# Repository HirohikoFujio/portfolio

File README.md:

# portfolio
## 内容物
* 3rd_year
    * late_team_dev
      * 後期チーム開発作成物 
    * seminar
      * 組込みゼミ作成物
* index
    * 作成物リンク集の予定(現在は空)

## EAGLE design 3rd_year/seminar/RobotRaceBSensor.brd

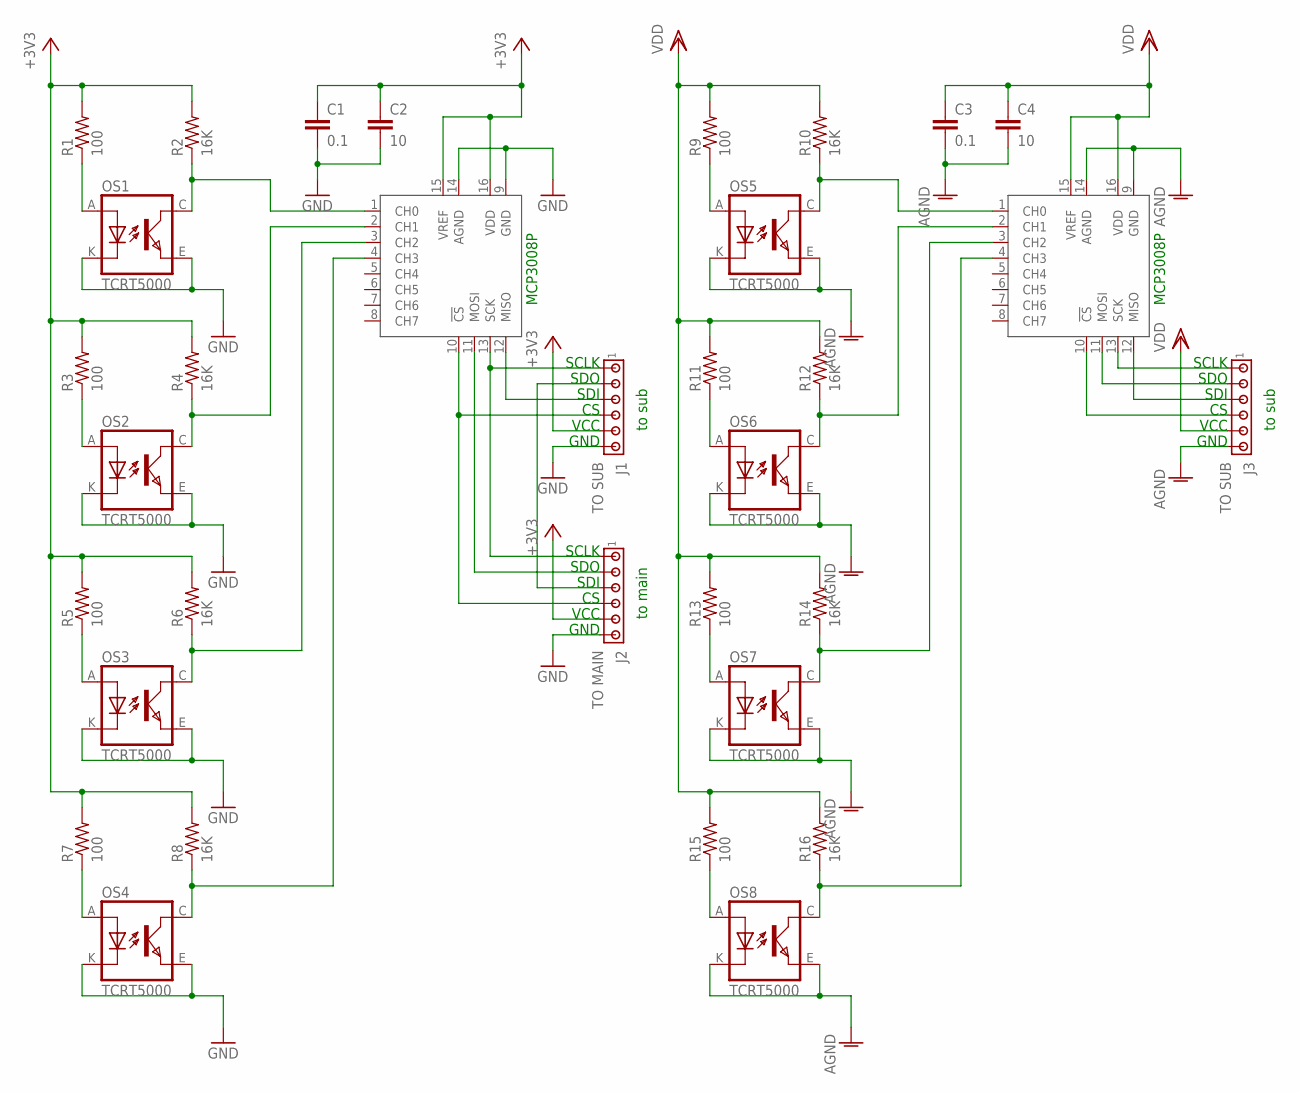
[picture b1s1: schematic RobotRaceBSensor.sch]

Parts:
C1, C3: 0.1; C0805
C2, C4: 10; C0805
J1, J3: TO SUB; 10X06MTA
J2: TO MAIN; 10X06MTA
OS1, OS2, OS3, OS4, OS5, OS6, OS7, OS8: TCRT5000
R1, R3, R5, R7, R9, R11, R13, R15: 100; R0805
R2, R4, R6, R8, R10, R12, R14, R16: 16K; R0805
U$1, U$2: MCP3008P; DIL16

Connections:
+3V3: C1.1, C2.1, J1.5, J2.5, R1.2, R2.2, R3.2, R4.2, R5.2, R6.2, R7.2, R8.2, U$1.15 (VREF), U$1.16 (VDD)
AGND: C3.2, C4.2, J3.6, OS5.E (EMITTER), OS5.K (CATHODE), OS6.E (EMITTER), OS6.K (CATHODE), OS7.E (EMITTER), OS7.K (CATHODE), OS8.E (EMITTER), OS8.K (CATHODE), U$2.9 (GND), U$2.14 (AGND)
GND: C1.2, C2.2, J1.6, J2.6, OS1.E (EMITTER), OS1.K (CATHODE), OS2.E (EMITTER), OS2.K (CATHODE), OS3.E (EMITTER), OS3.K (CATHODE), OS4.E (EMITTER), OS4.K (CATHODE), U$1.9 (GND), U$1.14 (AGND)
unnamed: OS1.A (ANODE), R1.1
unnamed: OS1.C (COLLECTOR), R2.1, U$1.1 (CH0)
unnamed: J1.1, J2.1, U$1.13 (SCK)
unnamed: OS2.A (ANODE), R3.1
unnamed: OS2.C (COLLECTOR), R4.1, U$1.2 (CH1)
unnamed: J1.3, U$1.12 (MISO)
unnamed: OS3.A (ANODE), R5.1
unnamed: OS3.C (COLLECTOR), R6.1, U$1.3 (CH2)
unnamed: J1.2, J2.3
unnamed: OS4.A (ANODE), R7.1
unnamed: OS4.C (COLLECTOR), R8.1, U$1.4 (CH3)
unnamed: J1.4, J2.4, U$1.10 (!CS)
unnamed: J2.2, U$1.11 (MOSI)
unnamed: OS5.A (ANODE), R9.1
unnamed: OS5.C (COLLECTOR), R10.1, U$2.1 (CH0)
unnamed: OS6.A (ANODE), R11.1
unnamed: OS6.C (COLLECTOR), R12.1, U$2.2 (CH1)
unnamed: OS7.A (ANODE), R13.1
unnamed: OS7.C (COLLECTOR), R14.1, U$2.3 (CH2)
unnamed: OS8.A (ANODE), R15.1
unnamed: OS8.C (COLLECTOR), R16.1, U$2.4 (CH3)
unnamed: J3.1, U$2.13 (SCK)
unnamed: J3.3, U$2.12 (MISO)
unnamed: J3.2, U$2.11 (MOSI)
unnamed: J3.4, U$2.10 (!CS)
VDD: C3.1, C4.1, J3.5, R9.2, R10.2, R11.2, R12.2, R13.2, R14.2, R15.2, R16.2, U$2.15 (VREF), U$2.16 (VDD)

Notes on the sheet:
SCLK
SDO
SDI
VCC
GND
MCP3008P
to main
to sub

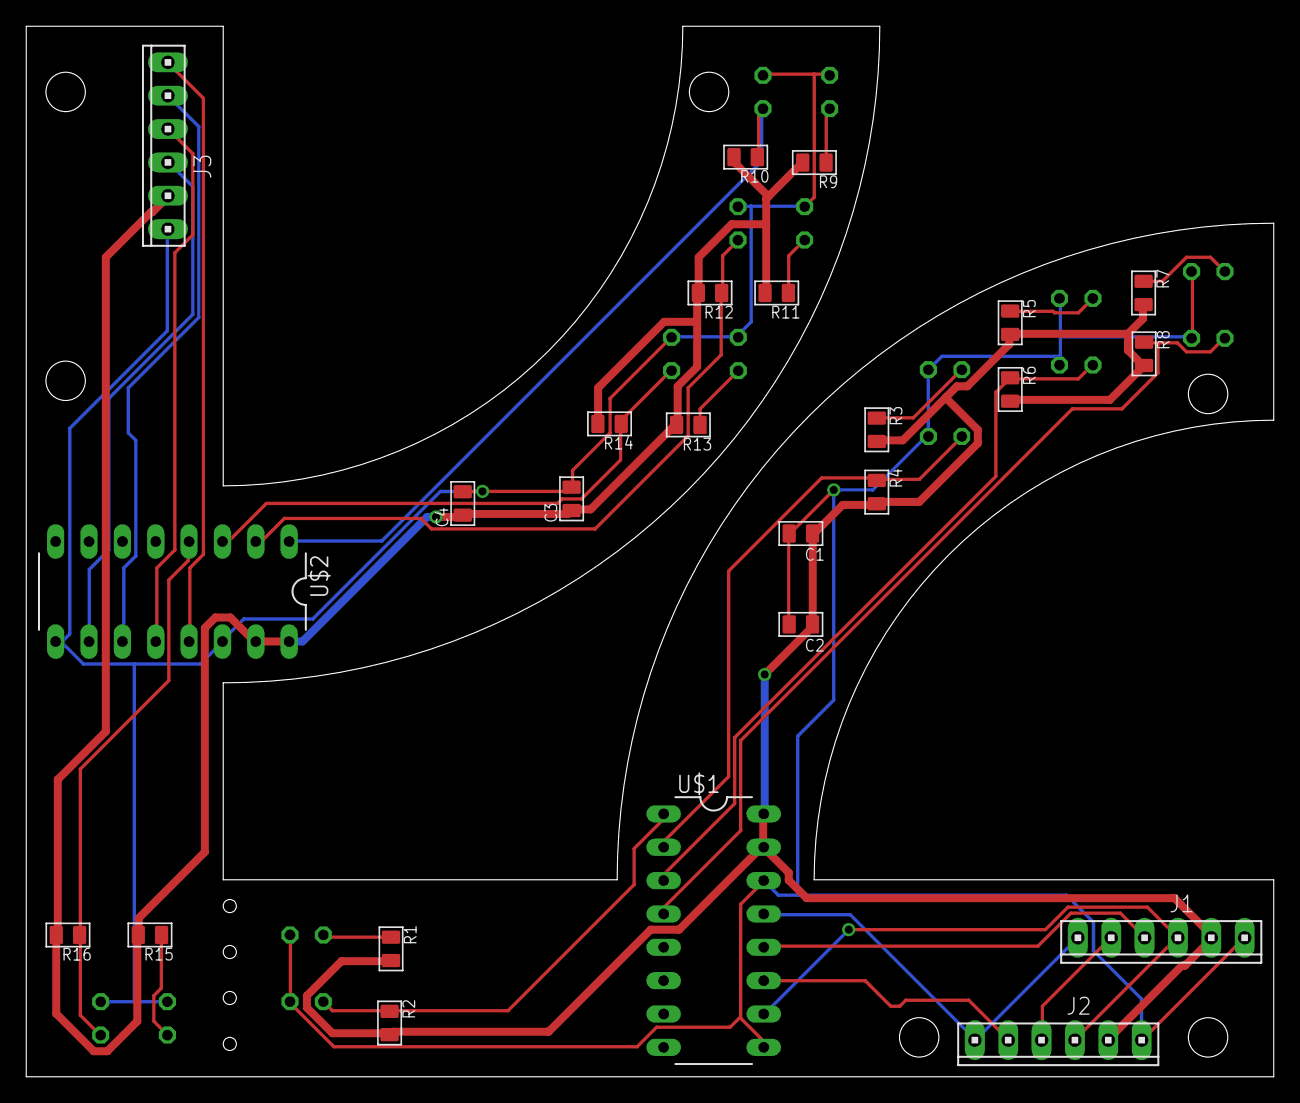
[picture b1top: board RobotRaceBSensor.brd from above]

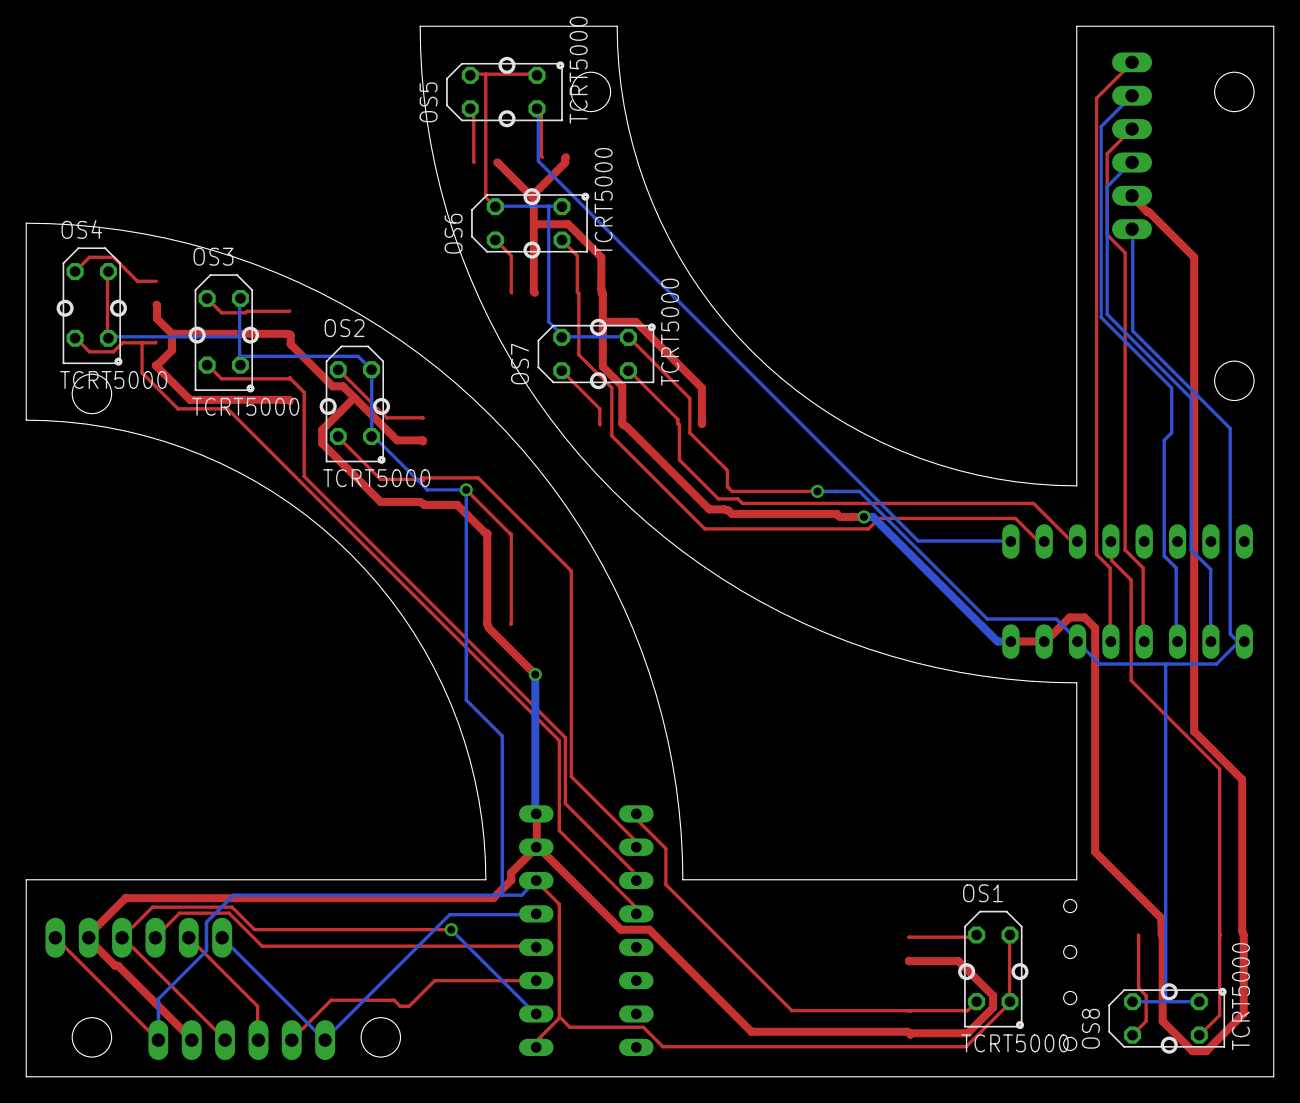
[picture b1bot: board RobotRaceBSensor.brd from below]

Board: 2 copper layers, 95.0 x 80.0 mm, 33 parts (8 on the bottom side), 29 nets.

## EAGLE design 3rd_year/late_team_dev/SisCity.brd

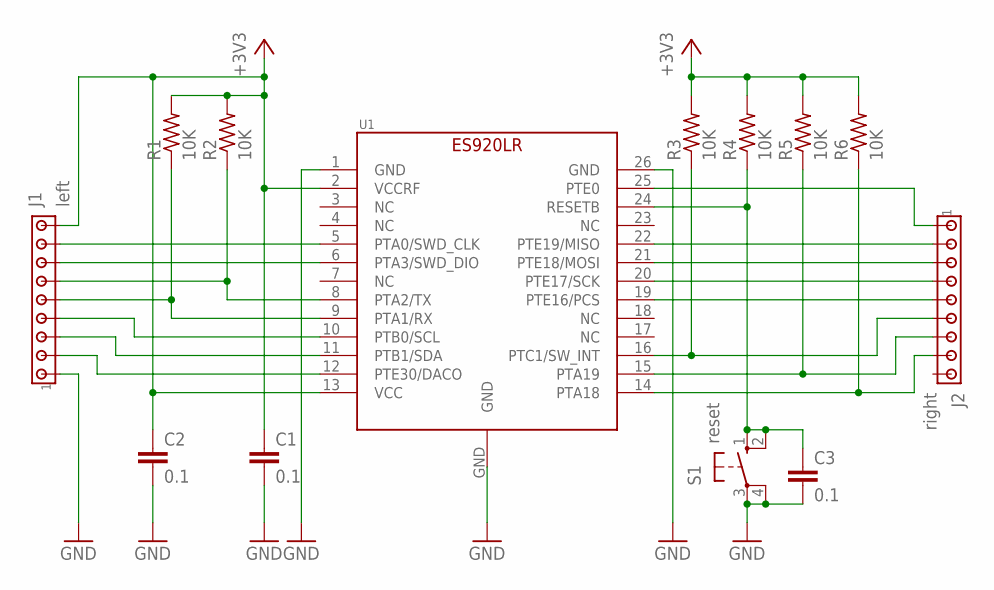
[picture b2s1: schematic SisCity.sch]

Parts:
C1, C2, C3: 0.1; C0805
J1: left; 10X09MTA
J2: right; 10X09MTA
R1, R2, R3, R4, R5, R6: 10K; M0805
S1: reset; B3F-10XX
U1: ES920LR

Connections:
+3V3: C1.1, C2.1, J1.9, R1.2, R2.2, R3.2, R4.2, R5.2, R6.2, U1.2 (VCCRF), U1.13 (VCC)
GND: C1.2, C2.2, C3.2, J1.1, S1.3, S1.4 (P1), U1.1 (GND), U1.26 (GND), U1.GND
unnamed: J1.8, U1.5 (PTA0/SWD_CLK)
unnamed: J1.7, U1.6 (PTA3/SWD_DIO)
unnamed: J1.4, U1.10 (PTB0/SCL)
unnamed: J1.6, R2.1, U1.8 (PTA2/TX)
unnamed: J1.5, R1.1, U1.9 (PTA1/RX)
unnamed: J1.3, U1.11 (PTB1/SDA)
unnamed: J1.2, U1.12 (PTE30/DACO)
unnamed: J2.1, U1.25 (PTE0)
unnamed: J2.2, U1.22 (PTE19/MISO)
unnamed: J2.3, U1.21 (PTE18/MOSI)
unnamed: J2.4, U1.20 (PTE17/SCK)
unnamed: J2.5, U1.19 (PTE16/PCS)
unnamed: J2.8, R6.1, U1.14 (PTA18)
unnamed: J2.7, R5.1, U1.15 (PTA19)
unnamed: J2.6, R3.1, U1.16 (PTC1/SW_INT)
unnamed: C3.1, R4.1, S1.1 (S), S1.2 (S1), U1.24 (RESETB)

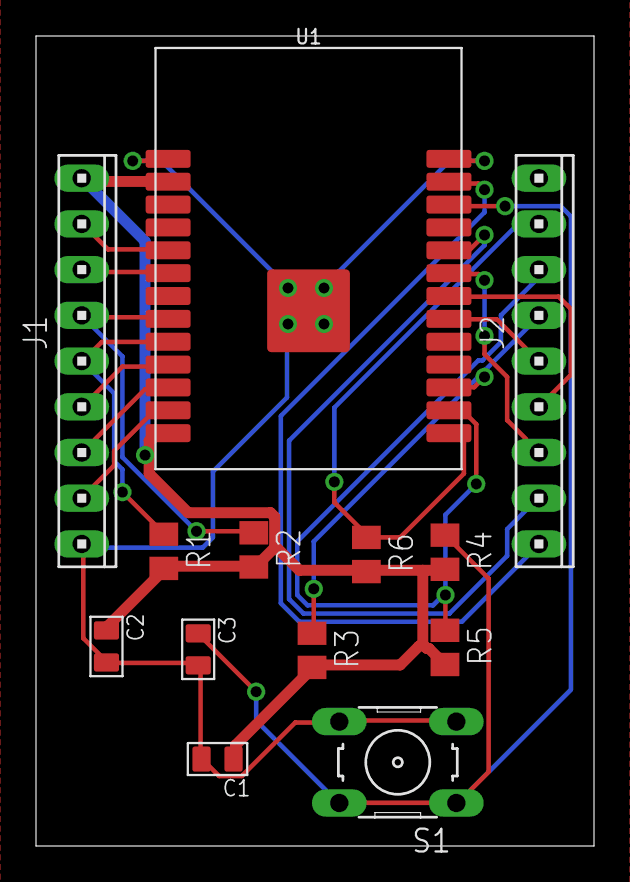
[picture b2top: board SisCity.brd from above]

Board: 2 copper layers, 31.0 x 45.0 mm, 13 parts (0 on the bottom side), 18 nets.

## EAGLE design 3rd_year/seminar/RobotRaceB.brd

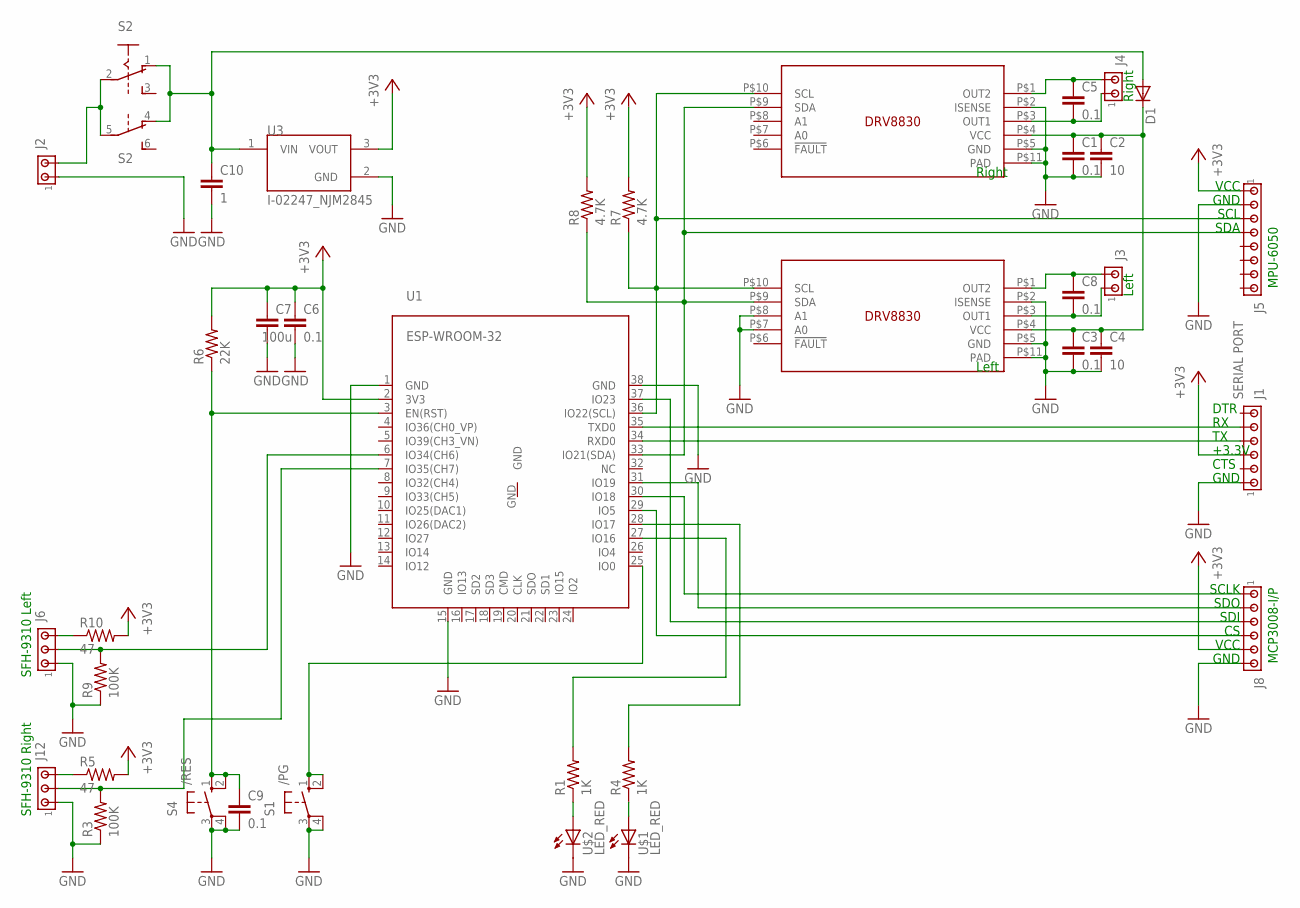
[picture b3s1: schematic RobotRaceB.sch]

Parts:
C1, C3, C5, C6, C8, C9: 0.1; C0805
C2, C4: 10; C0805
C7: 100u; C0805
C10: 1; C0805
D1: DIODE-D-10; D-10
J1: SERIAL PORT; 10X06MTA
J2, J3, J4: MTA02-100; 10X02MTA
J5: MTA08-100; 10X08MTA
J6, J12: MTA03-100; 10X03MTA
J8: MTA06-100; 10X06MTA
R1, R4: 1K; M0805
R3, R9: 100K; M0805
R5, R10: 47; M0805
R6: 22K; M0805
R7, R8: 4.7K; R0805
S1: /PG; B3F-10XX
S2: SLIDE_SW_6P; A68-A31
S4: /RES; B3F-10XX
U1: ESP-WROOM-32
U3: I-02247_NJM2845; TO252
U$1, U$2: LED_RED; LED_LEAD
U$4, U$6: DRV8830

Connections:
+3V1: C10.1, D1.A, S2.1 (O), S2.4 (O), U3.1 (VIN)
+3V3: C6.1, C7.1, J1.3, J5.1, J8.5, R5.2, R6.2, R7.2, R8.2, R10.2, U1.2 (3V3), U3.3 (VOUT)
GND: C1.2, C2.2, C3.2, C4.2, C6.2, C7.2, C9.2, C10.2, J1.1, J2.1, J5.2, J6.1, J8.6, J12.1, R3.1, R9.1, S1.3, S1.4 (P1), S4.3, S4.4 (P1), U1.1 (GND), U1.15 (GND), U1.38 (GND), U3.2 (GND), U$1.K (C), U$2.K (C), U$4.P$2 (ISENSE), U$4.P$5 (GND), U$4.P$11 (PAD), U$6.P$2 (ISENSE), U$6.P$5 (GND), U$6.P$7 (A0), U$6.P$8 (A1), U$6.P$11 (PAD)
unnamed: R4.1, U$1.A
unnamed: J2.2, S2.2, S2.5
unnamed: C8.1, J3.2, U$6.P$1 (OUT2)
unnamed: C8.2, J3.1, U$6.P$3 (OUT1)
unnamed: C5.2, J4.1, U$4.P$3 (OUT1)
unnamed: R1.1, U$2.A
unnamed: C9.1, R6.1, S4.1 (S), S4.2 (S1), U1.3 (EN(RST))
unnamed: J8.1, U1.30 (IO18)
unnamed: J8.2, U1.31 (IO19)
unnamed: J5.3, R7.1, U1.36 (IO22(SCL)), U$4.P$10 (SCL), U$6.P$10 (SCL)
unnamed: J12.3, R5.1
unnamed: J6.2, R9.2, U1.6 (IO34(CH6))
unnamed: C5.1, J4.2, U$4.P$1 (OUT2)
unnamed: R1.2, U1.27 (IO16)
unnamed: J1.5, U1.35 (TXD0)
unnamed: J5.4, R8.1, U1.33 (IO21(SDA)), U$4.P$9 (SDA), U$6.P$9 (SDA)
unnamed: J1.4, U1.34 (RXD0)
unnamed: R4.2, U1.28 (IO17)
unnamed: J8.3, U1.37 (IO23)
unnamed: J8.4, U1.29 (IO5)
unnamed: S1.1 (S), S1.2 (S1), U1.25 (IO0)
unnamed: J6.3, R10.1
unnamed: J12.2, R3.2, U1.7 (IO35(CH7))
unnamed: C1.1, C2.1, C3.1, C4.1, D1.C, U$4.P$4 (VCC), U$6.P$4 (VCC)

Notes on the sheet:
DTR
+3.3V
CTS
GND
VCC
SCL
SDA
SCLK
SDO
SDI
MPU-6050
MCP3008-I/P
SFH-9310 Left
SFH-9310 Right
Right
Left

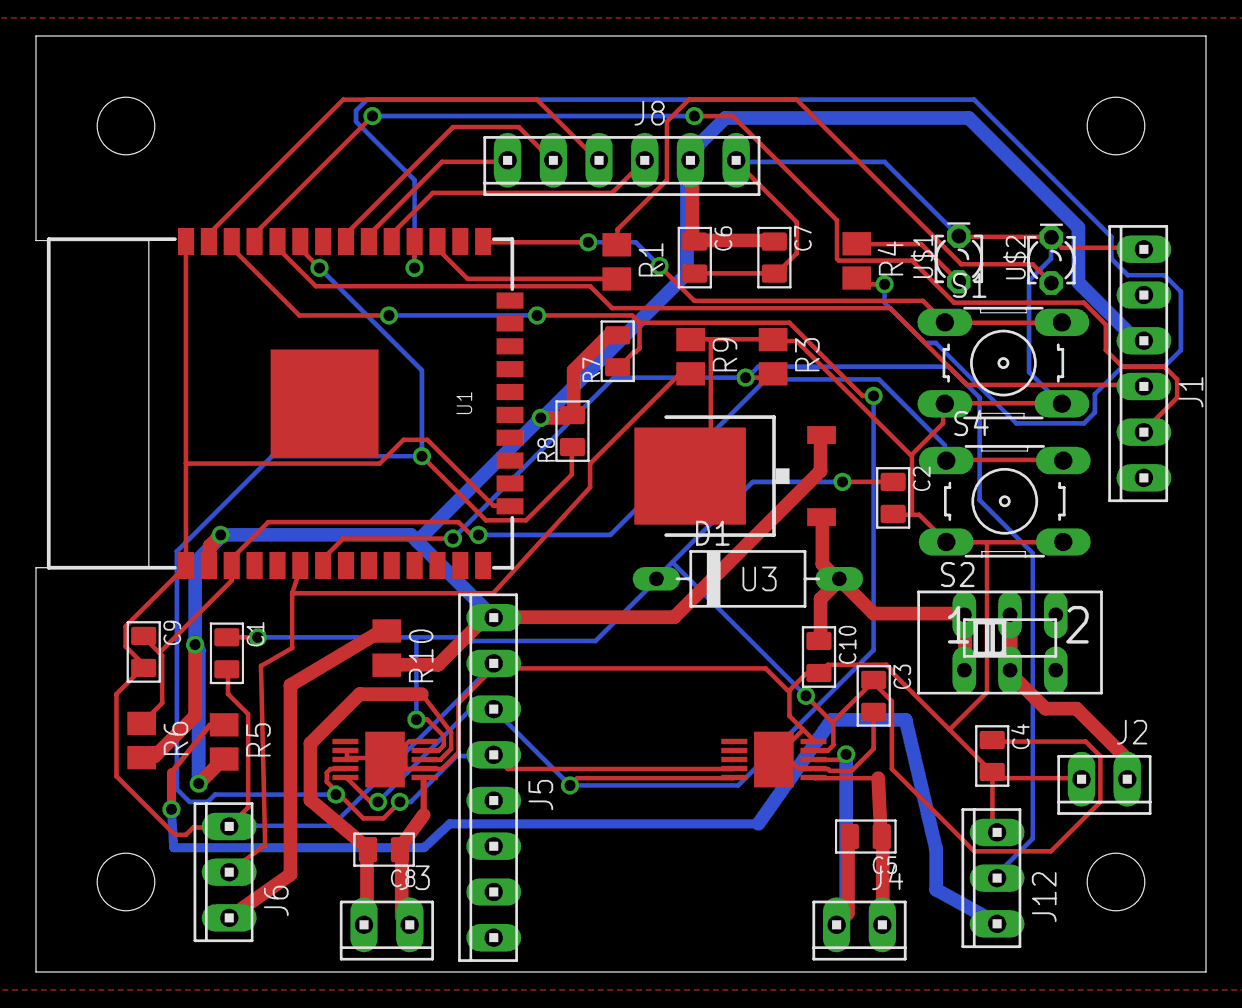
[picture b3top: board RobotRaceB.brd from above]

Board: 2 copper layers, 65.0 x 52.0 mm, 37 parts (0 on the bottom side), 27 nets.

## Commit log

2022-02-09 upload file
2022-02-09 add images

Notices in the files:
parts and their libraries:
FaBo-LoRa: Released under the Creative Commons Attribution-ShareAlike 4.0 License
https://creativecommons.org/licenses/by-sa/4.0
